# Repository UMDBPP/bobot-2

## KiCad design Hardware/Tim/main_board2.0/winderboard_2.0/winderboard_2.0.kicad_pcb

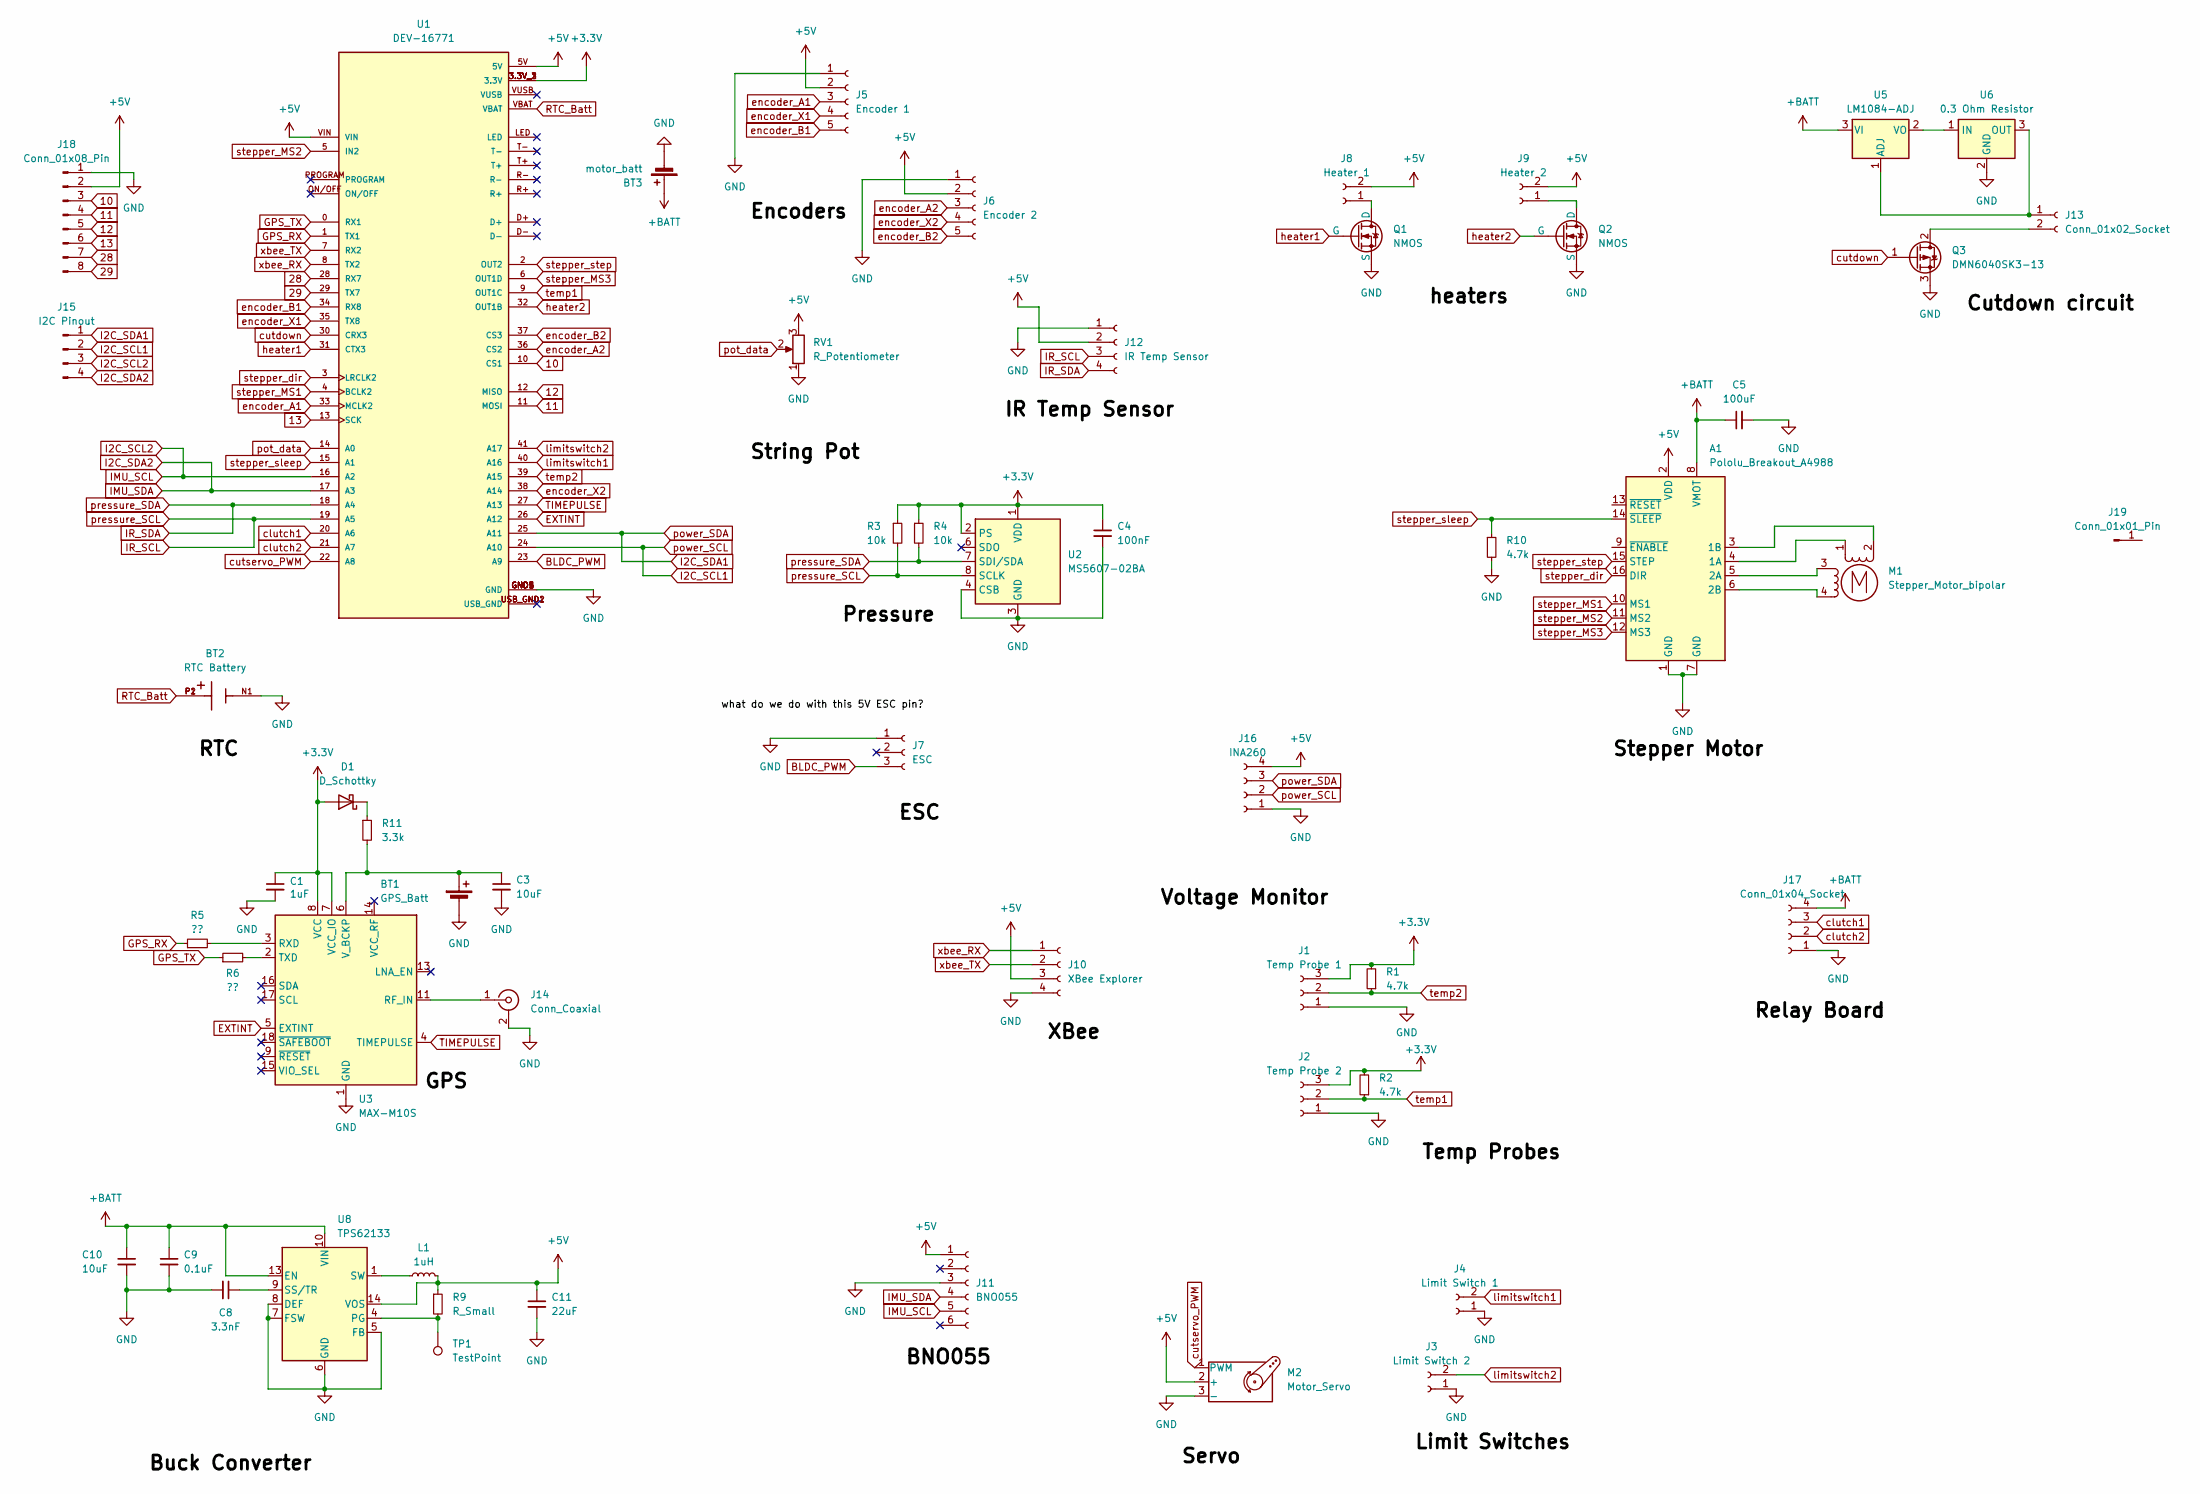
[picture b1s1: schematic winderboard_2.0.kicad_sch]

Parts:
A1: Pololu_Breakout_A4988; Pololu_Breakout-16_15.2x20.3mm
BT1: GPS_Batt; SEIKO_ML414H_IV01E
BT2: RTC Battery; BAT_BAT-HLD-001; PARTREV C
BT3: motor_batt; AMASS_XT30PW-M_1x02_P2.50mm_Horizontal
C1: 1uF; C_0603_1608Metric_Pad1.08x0.95mm_HandSolder
C3, C10: 10uF; C_0603_1608Metric_Pad1.08x0.95mm_HandSolder
C4: 100nF; C_0603_1608Metric_Pad1.08x0.95mm_HandSolder
C5: 100uF; C_0603_1608Metric_Pad1.08x0.95mm_HandSolder
C8: 3.3nF; C_0603_1608Metric_Pad1.08x0.95mm_HandSolder
C9: 0.1uF; C_0603_1608Metric_Pad1.08x0.95mm_HandSolder
C11: 22uF; C_0603_1608Metric_Pad1.08x0.95mm_HandSolder
D1: D_Schottky; D_SOD-123F
J1: Temp Probe 1; JST_XH_B3B-XH-A_1x03_P2.50mm_Vertical
J2: Temp Probe 2; JST_XH_B3B-XH-A_1x03_P2.50mm_Vertical
J3: Limit Switch 2; JST_XH_B2B-XH-A_1x02_P2.50mm_Vertical
J4: Limit Switch 1; JST_XH_B2B-XH-A_1x02_P2.50mm_Vertical
J5: Encoder 1; JST_XH_B5B-XH-A_1x05_P2.50mm_Vertical
J6: Encoder 2; JST_XH_B5B-XH-A_1x05_P2.50mm_Vertical
J7: ESC; JST_XH_B3B-XH-A_1x03_P2.50mm_Vertical
J8: Heater 1; JST_XH_B2B-XH-A_1x02_P2.50mm_Vertical
J9: Heater 2; JST_XH_B2B-XH-A_1x02_P2.50mm_Vertical
J10: XBee Explorer
J11: BNO055
J12: IR Temp Sensor; JST_XH_B4B-XH-A_1x04_P2.50mm_Vertical
J13: Conn_01x02_Socket; PinHeader_1x02_P2.54mm_Vertical
J14: Conn_Coaxial; U.FL_Molex_MCRF_73412-0110_Vertical
J15: I2C Pinout; PinHeader_1x04_P2.54mm_Vertical
J16: INA260; JST_XH_B4B-XH-A_1x04_P2.50mm_Vertical
J17: Conn_01x04_Socket; JST_XH_B4B-XH-A_1x04_P2.50mm_Vertical
J18: Conn_01x08_Pin; PinHeader_1x08_P2.54mm_Vertical
J19: Conn_01x01_Pin; MountingHole_3.2mm_M3_DIN965_Pad
L1: 1uH; L_Coilcraft_XxL4040
M1: Stepper_Motor_bipolar; JST_XH_B4B-XH-A_1x04_P2.50mm_Vertical
M2: Motor_Servo; JST_XH_B3B-XH-A_1x03_P2.50mm_Vertical
Q1, Q2: NMOS; SOT-23-3
Q3: DMN6040SK3-13; TO-252-2
R1, R2, R10: 4.7k; R_0603_1608Metric_Pad0.98x0.95mm_HandSolder
R3, R4: 10k; R_0603_1608Metric_Pad0.98x0.95mm_HandSolder
R5, R6: ??; R_0603_1608Metric_Pad0.98x0.95mm_HandSolder
R9: R_Small; R_0603_1608Metric_Pad0.98x0.95mm_HandSolder
R11: 3.3k; R_0603_1608Metric_Pad0.98x0.95mm_HandSolder
RV1: R_Potentiometer; JST_XH_B3B-XH-A_1x03_P2.50mm_Vertical
TP1: TestPoint; TestPoint_Loop_D2.54mm_Drill1.5mm_Beaded
U1: DEV-16771; MODULE_DEV-16771; PARTREV 4.1
U2: MS5607-02BA; LGA-8_3x5mm_P1.25mm
U3: MAX-M10S; ublox_MAX
U5: LM1084-ADJ; TO-263-3_TabPin2
U6: 0.3 Ohm Resistor; TO-263-2
U8: TPS62133; VQFN-16-1EP_3x3mm_P0.5mm_EP1.68x1.68mm_ThermalVias

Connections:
10: J18.3, U1.10 (CS1)
11: J18.4, U1.11 (MOSI)
12: J18.5, U1.12 (MISO)
13: J18.6, U1.13 (SCK)
28: J18.7, U1.28 (RX7)
29: J18.8, U1.29 (TX7)
+3.3V: C1.1, C4.1, D1.2 (A), J1.3, J2.3, R1.2, R2.2, R3.1, R4.1, U1.3.3V_1 (3.3V), U1.3.3V_2 (3.3V), U1.3.3V_3 (3.3V), U2.1 (VDD), U2.2 (PS), U3.7 (VCC_IO), U3.8 (VCC)
+5V: A1.2 (VDD), C11.1, J5.2, J6.2, J8.2, J9.2, J10.3, J11.1, J12.2, J16.4, J18.2, L1.2, M2.2 (+), R9.1, RV1.3, U1.5V, U1.VIN, U8.14 (VOS)
+BATT: A1.8 (VMOT), BT3.1 (+), C5.1, C9.1, C10.1, J17.4, U5.3 (VI), U8.10 (VIN), U8.11 (VIN), U8.12 (VIN), U8.13 (EN)
BLDC_PWM: J7.3, U1.23 (A9)
EXTINT: U1.26 (A12), U3.5 (EXTINT)
GND: A1.1 (GND), A1.7 (GND), BT1.2 (-), BT2.N1, BT3.2 (-), C1.2, C3.2, C4.2, C5.2, C8.2, C9.2, C10.2, C11.2, J1.1, J2.1, J3.1, J4.1, J5.1, J6.1, J7.1, J10.4, J11.3, J12.1, J14.2 (Ext), J16.1, J17.1, J18.1, M2.3 (-), Q1.3 (S), Q2.3 (S), Q3.3 (S), R10.2, RV1.1, U1.GND1 (GND), U1.GND2 (GND), U1.GND3 (GND), U1.GND4 (GND), U1.GND5 (GND), U2.3 (GND), U2.4 (CSB), U2.5 (CSB), U3.1 (GND), U3.10 (GND), U3.12 (GND), U6.2 (GND), U8.5 (FB), U8.6 (GND), U8.7 (FSW), U8.8 (DEF), U8.15 (GND), U8.16 (GND), U8.17 (GND)
GPS_RX: R5.1, U1.1 (TX1)
GPS_TX: R6.1, U1.0 (RX1)
I2C_SCL1: J15.2, J16.2, U1.24 (A10)
I2C_SCL2: J11.5, J15.3, U1.16 (A2)
I2C_SDA1: J15.1, J16.3, U1.25 (A11)
I2C_SDA2: J11.4, J15.4, U1.17 (A3)
IR_SCL: J12.3, R3.2, U1.19 (A5), U2.8 (SCLK)
IR_SDA: J12.4, R4.2, U1.18 (A4), U2.7 (SDI/SDA)
unnamed: A1.4 (1A), M1.1
unnamed: A1.3 (1B), M1.2 (-)
unnamed: A1.5 (2A), M1.3
unnamed: A1.6 (2B), M1.4
unnamed: BT1.1 (+), C3.1, R11.2, U3.6 (V_BCKP)
unnamed: D1.1 (K), R11.1
unnamed: J8.1, Q1.1 (D)
unnamed: J9.1, Q2.1 (D)
unnamed: J13.1, U5.1 (ADJ), U6.3 (OUT)
unnamed: J13.2, Q3.2 (D)
unnamed: J14.1 (In), U3.11 (RF_IN)
unnamed: L1.1, U8.1 (SW), U8.2 (SW), U8.3 (SW)
unnamed: R5.2, U3.3 (RXD)
unnamed: R6.2, U3.2 (TXD)
unnamed: U5.2 (VO), U6.1 (IN)
unnamed: R9.2, TP1.1, U8.4 (PG)
unnamed: C8.1, U8.9 (SS/TR)
RTC_Batt: BT2.P1, BT2.P2, U1.VBAT
TIMEPULSE: U1.27 (A13), U3.4 (TIMEPULSE)
clutch1: J17.3, U1.20 (A6)
clutch2: J17.2, U1.21 (A7)
cutdown: Q3.1 (G), U1.30 (CRX3)
cutservo_PWM: M2.1 (PWM), U1.22 (A8)
encoder_A1: J5.3, U1.33 (MCLK2)
encoder_A2: J6.3, U1.36 (CS2)
encoder_B1: J5.5, U1.34 (RX8)
encoder_B2: J6.5, U1.37 (CS3)
encoder_X1: J5.4, U1.35 (TX8)
encoder_X2: J6.4, U1.38 (A14)
heater1: Q1.2 (G), U1.31 (CTX3)
heater2: Q2.2 (G), U1.32 (OUT1B)
limitswitch1: J4.2, U1.40 (A16)
limitswitch2: J3.2, U1.41 (A17)
pot_data: RV1.2, U1.14 (A0)
stepper_MS1: A1.10 (MS1), U1.4 (BCLK2)
stepper_MS2: A1.11 (MS2), U1.5 (IN2)
stepper_MS3: A1.12 (MS3), U1.6 (OUT1D)
stepper_dir: A1.16 (DIR), U1.3 (LRCLK2)
stepper_sleep: A1.14 (~SLEEP), R10.1, U1.15 (A1)
stepper_step: A1.15 (STEP), U1.2 (OUT2)
temp1: J2.2, R2.1, U1.9 (OUT1C)
temp2: J1.2, R1.1, U1.39 (A15)
xbee_RX: J10.1, U1.8 (TX2)
xbee_TX: J10.2, U1.7 (RX2)

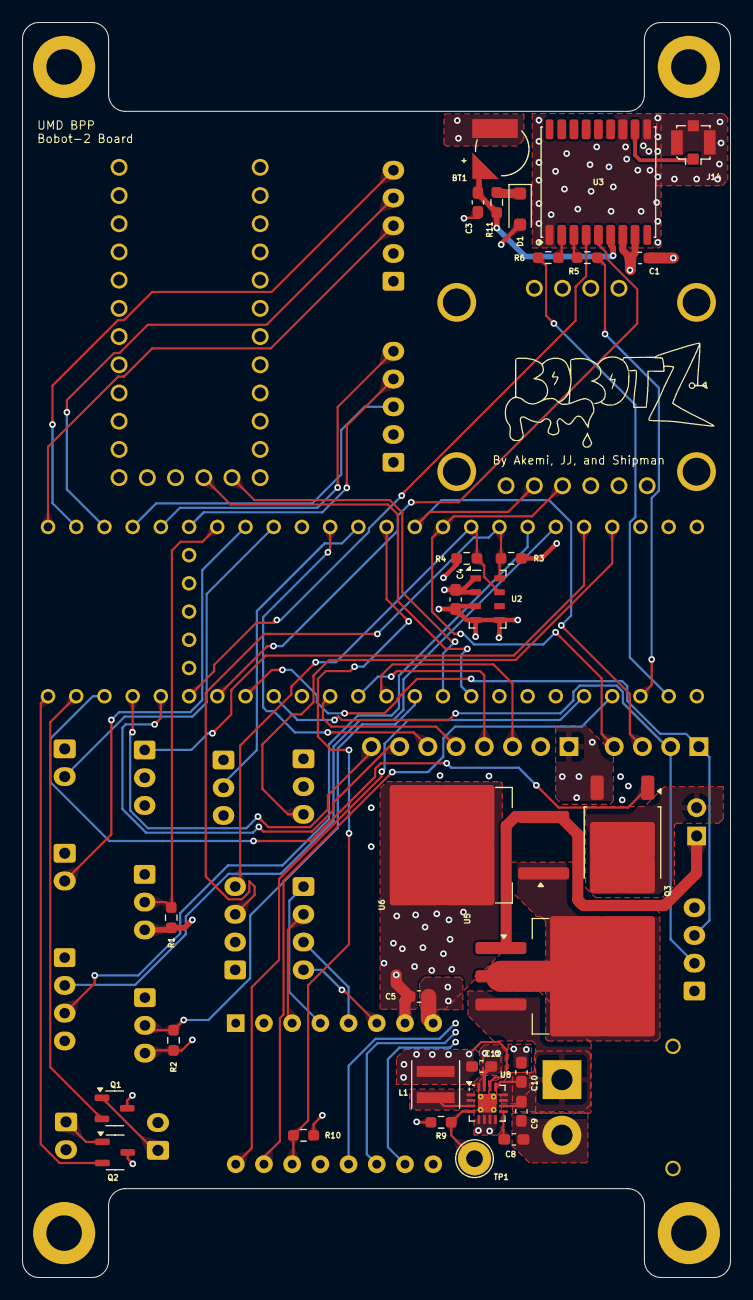
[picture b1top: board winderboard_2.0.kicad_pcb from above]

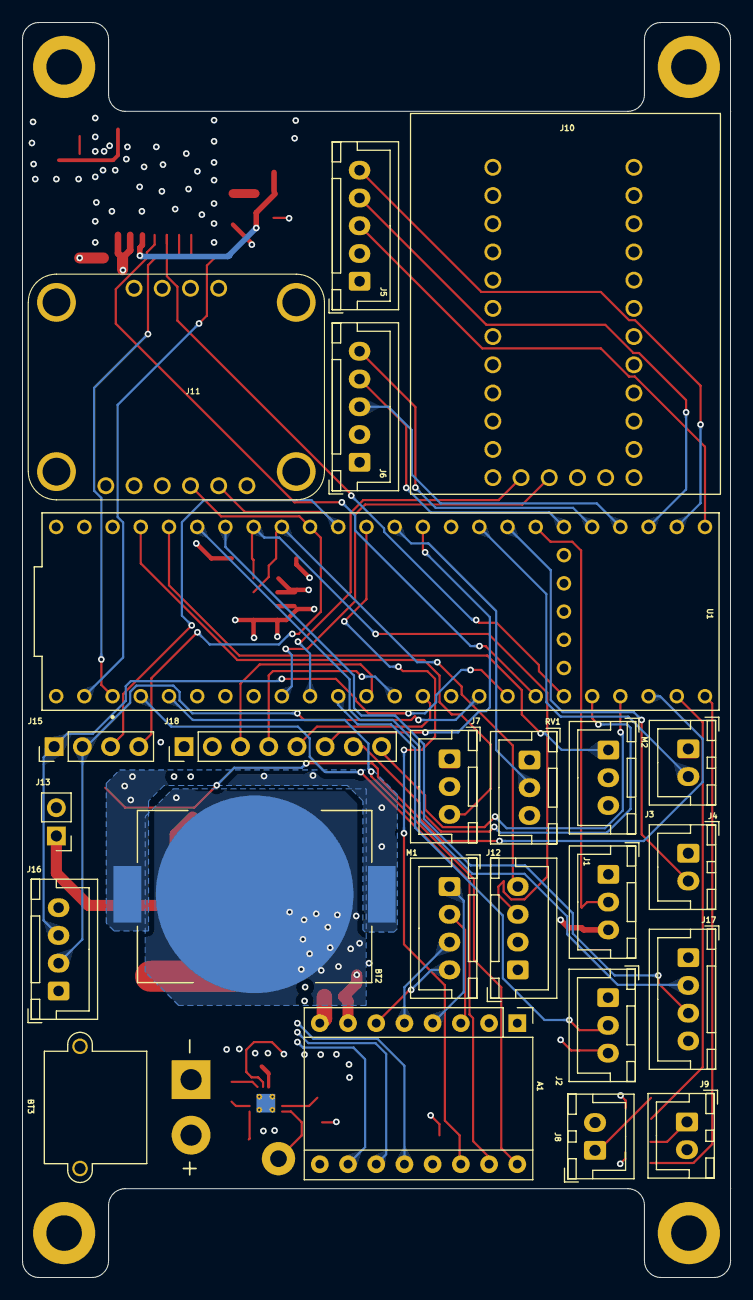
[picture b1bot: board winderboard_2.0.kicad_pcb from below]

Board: 4 copper layers, 63.8 x 113.0 mm, 58 parts (24 on the bottom side), 64 nets.

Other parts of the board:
J19#2, J19#3, J19#4: Conn_01x01_Pin; MountingHole_3.2mm_M3_DIN965_Pad

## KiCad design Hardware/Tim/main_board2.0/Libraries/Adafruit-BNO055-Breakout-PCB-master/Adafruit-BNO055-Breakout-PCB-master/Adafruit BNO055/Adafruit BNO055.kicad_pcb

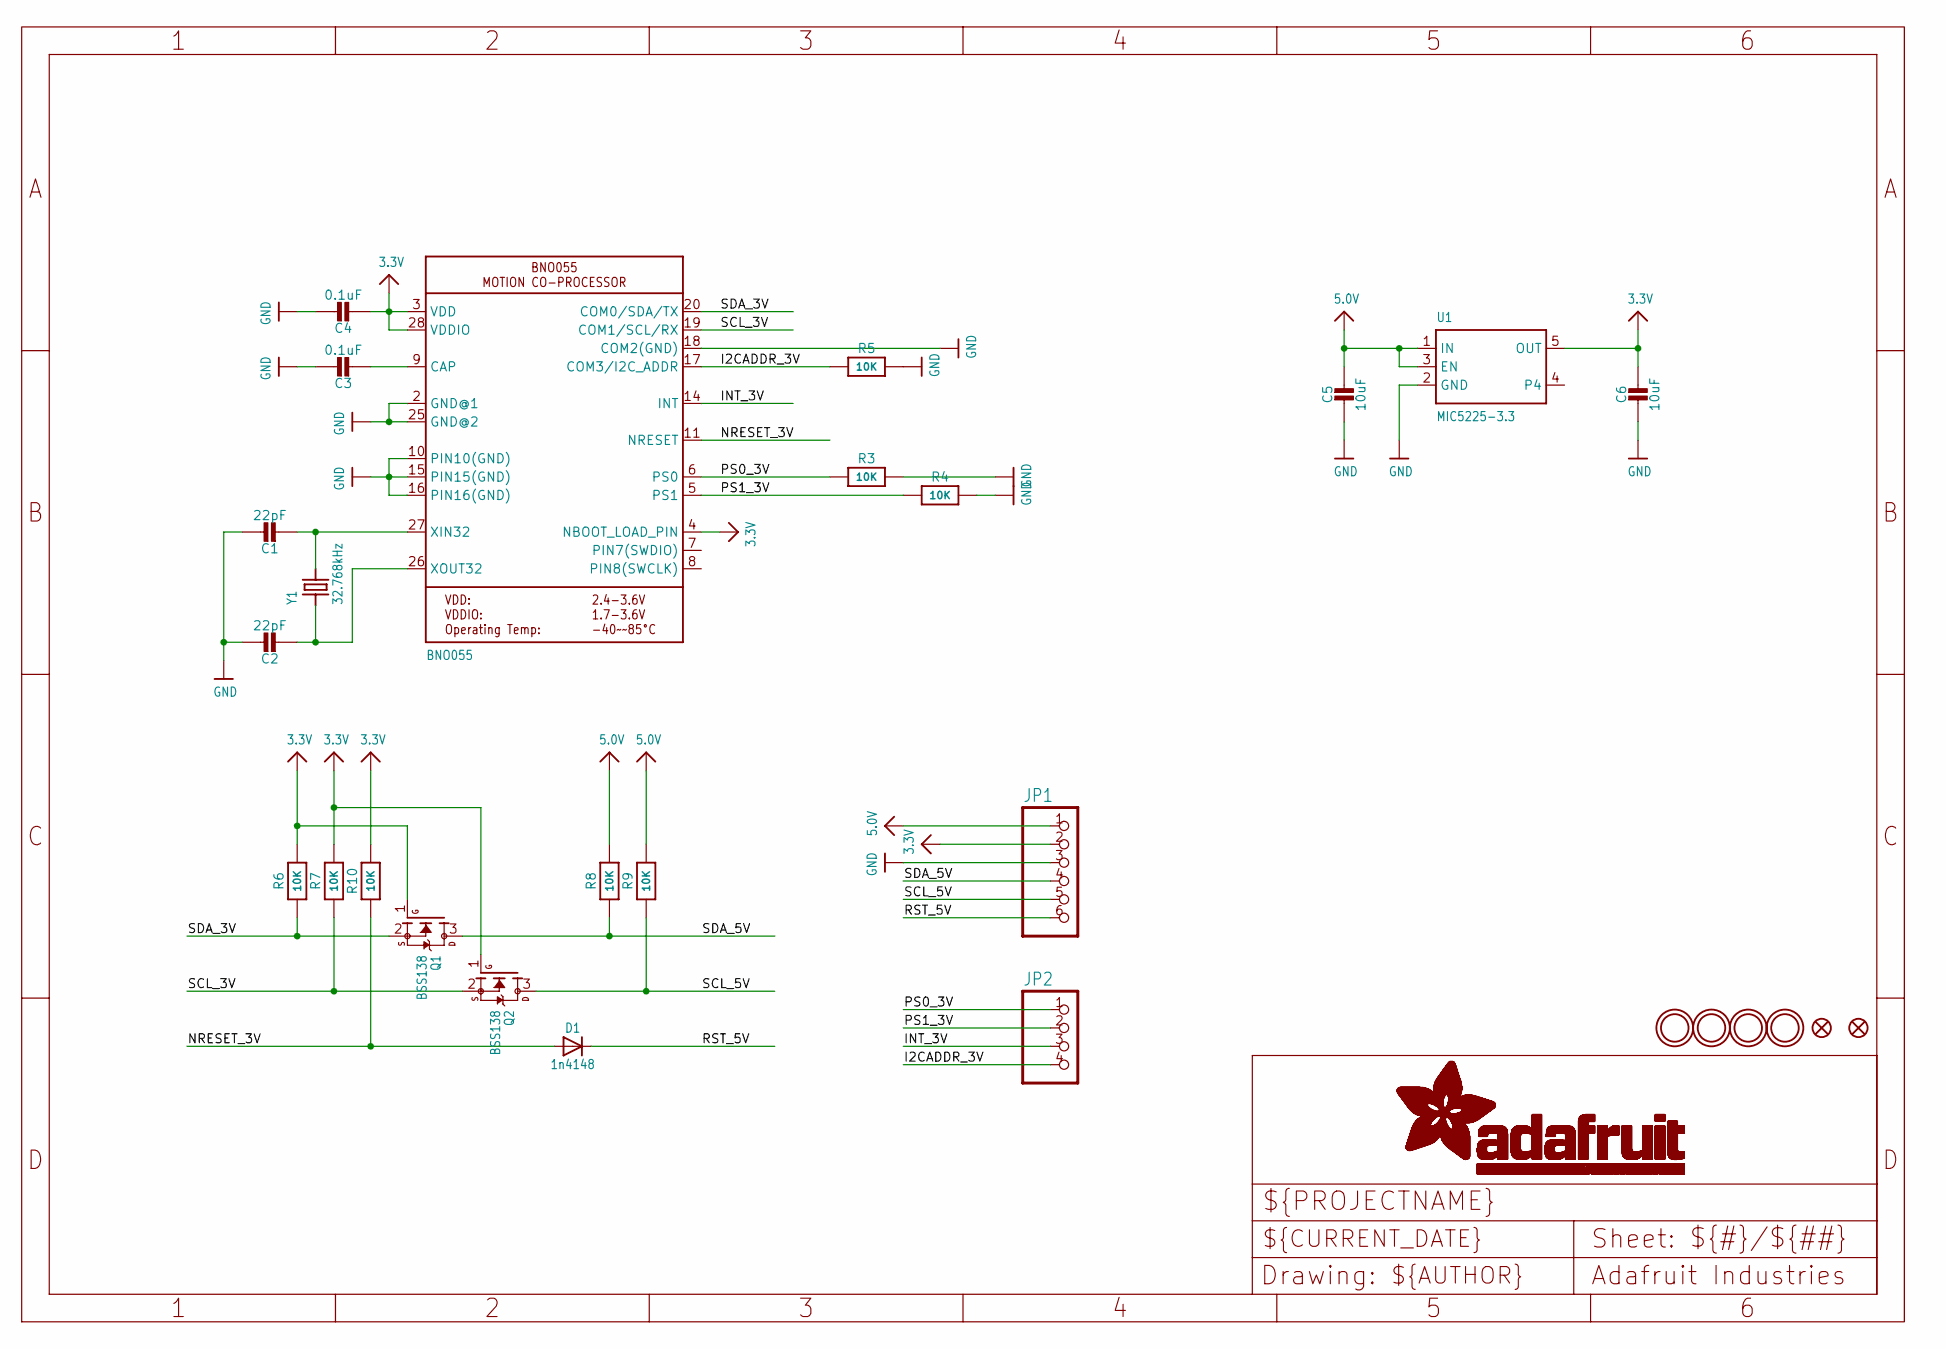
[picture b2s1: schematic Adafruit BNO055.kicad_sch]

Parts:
C1, C2: 22pF; 0805-NO
C3: 0.1uF; 0805-NO
C4: 0.1uF; 0805_10MGAP
C5: 10uF; 0805-NO
C6: 10uF; 0805_10MGAP
D1: 1n4148; SOD-323
FID1, FID2: FIDUCIAL""; FIDUCIAL_1MM
JP1: HEADER-1X676MIL; 1X06_ROUND_76
JP2: HEADER-1X476MIL; 1X04_ROUND_76
Q1, Q2: BSS138; SOT23-WIDE
R3, R4, R5, R6, R7, R10: 10K; 0805-NO
R8, R9: 10K; _0805MP
U1: MIC5225-3.3; SOT23-5
U$2: BNO055
U$29, U$30, U$31, U$32: MOUNTINGHOLE2.5_THICK; MOUNTINGHOLE_2.5_PLATED_THICK
Y1: 32.768kHz; CRYSTAL_8X3.8

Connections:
3.3V: C4.2, C6.1, JP1.2, Q1.1 (G), Q2.1 (G), R6.2, R7.2, R10.2, U1.5 (OUT), U$2.3 (VDD), U$2.4 (NBOOT_LOAD_PIN), U$2.28 (VDDIO)
5.0V: C5.1, JP1.1, R8.2, R9.2, U1.1 (IN), U1.3 (EN)
GND: C1.1, C2.1, C3.1, C4.1, C5.2, C6.2, JP1.3, R3.2, R4.2, R5.2, U1.2 (GND), U$2.2 (GND@1), U$2.10 (PIN10(GND)), U$2.15 (PIN15(GND)), U$2.16 (PIN16(GND)), U$2.18 (COM2(GND)), U$2.25 (GND@2)
I2CADDR_3V: JP2.4, R5.1, U$2.17 (COM3/I2C_ADDR)
INT_3V: JP2.3, U$2.14 (INT)
unnamed: C1.2, U$2.27 (XIN32), Y1.P$4 (2)
unnamed: C2.2, U$2.26 (XOUT32), Y1.P$1 (1)
unnamed: C3.2, U$2.9 (CAP)
NRESET_3V: D1.A, R10.1, U$2.11 (NRESET)
PS0_3V: JP2.1, R3.1, U$2.6 (PS0)
PS1_3V: JP2.2, R4.1, U$2.5 (PS1)
RST_5V: D1.C, JP1.6
SCL_3V: Q2.2 (S), R7.1, U$2.19 (COM1/SCL/RX)
SCL_5V: JP1.5, Q2.3 (D), R9.1
SDA_3V: Q1.2 (S), R6.1, U$2.20 (COM0/SDA/TX)
SDA_5V: JP1.4, Q1.3 (D), R8.1

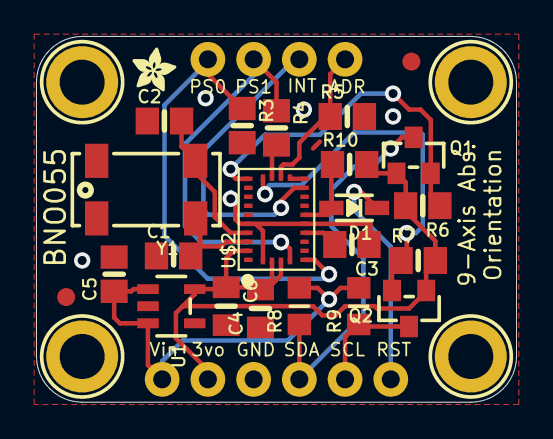
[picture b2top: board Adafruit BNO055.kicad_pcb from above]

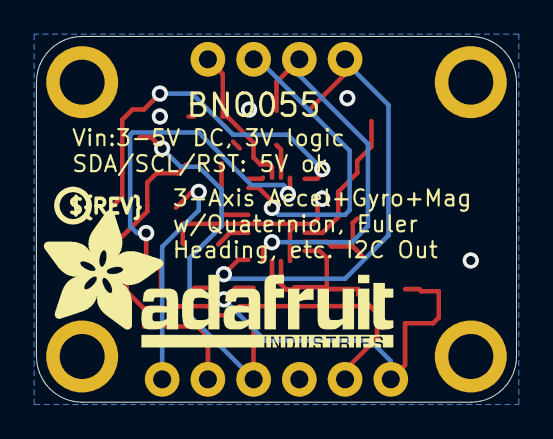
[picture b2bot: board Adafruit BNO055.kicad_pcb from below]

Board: 2 copper layers, 26.7 x 20.3 mm, 31 parts (2 on the bottom side), 16 nets.

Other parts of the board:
U$3: PCBFEAT-REV-040
U$28: ADAFRUIT_TEXT_20MM
U$33: ADAFRUIT_2.5MM

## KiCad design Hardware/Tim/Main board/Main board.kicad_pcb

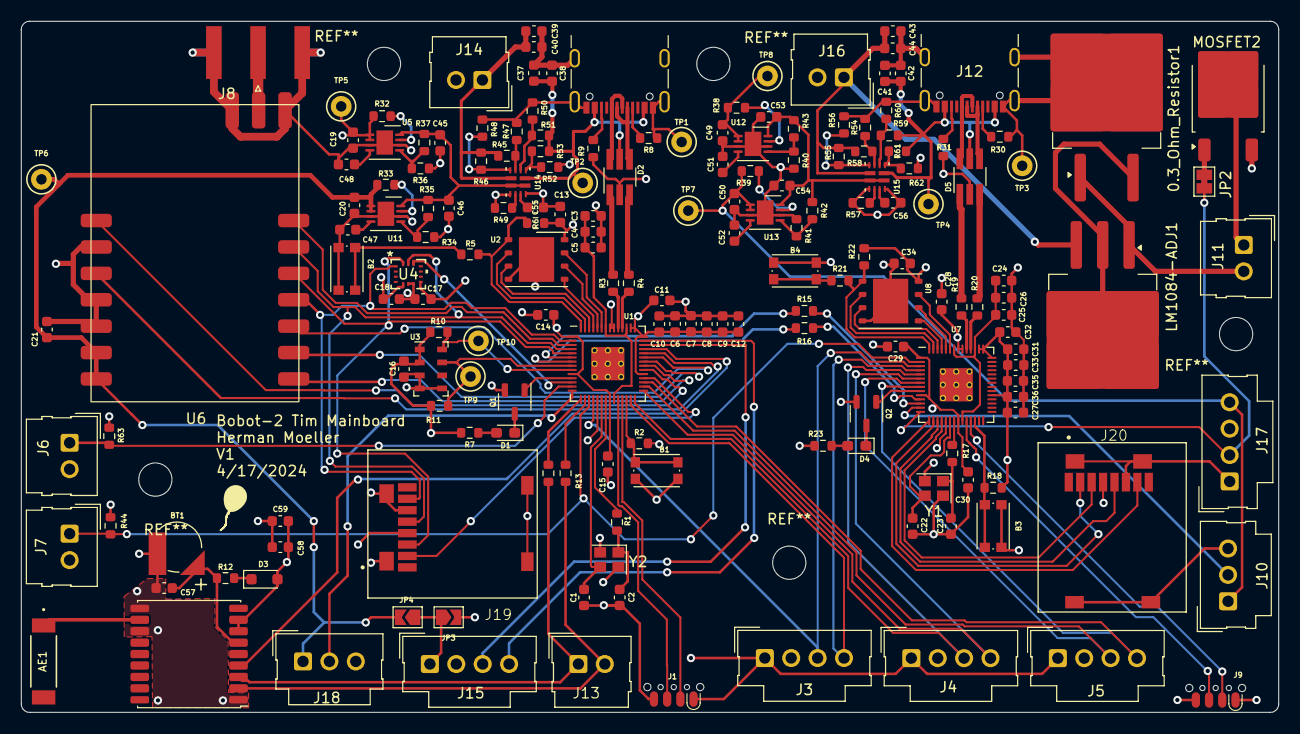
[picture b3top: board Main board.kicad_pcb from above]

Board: 4 copper layers, 121.0 x 66.5 mm, 181 parts (0 on the bottom side), 133 nets.

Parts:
0.3_Ohm_Resistor1: 03; TO-263-2
AE1: Antenna; ANT_1575AT_JOT-M
B1, B2, B3, B4: KMR2; SW_Push_1P1T_NO_CK_KMR2
BT1: ML414H IV01E; SEIKO_ML414H_IV01E
C1, C2, C22, C23: 10pF; C_0603_1608Metric
C3, C4, C7, C8, C9, C10, C12, C13, C14, C15, C16, C17, C18, C24, C25, C28, C29, C30, C31, C33, C34, C35, C36, C38, C40, C42, C44, C58: 100nF; C_0603_1608Metric
C5, C6, C19, C20, C26, C27, C37, C39, C41, C43, C45, C46, C49, C50, C53, C54, C55, C56, C59: 1uF; C_0603_1608Metric
C11, C21, C32, C57: 10uF; C_0603_1608Metric
C47, C48, C51, C52: 1nF; C_0603_1608Metric
D1, D4: LED; D_0603_1608Metric_Pad1.05x0.95mm_HandSolder
D2, D5: USBLC6-2SC6; TSOT-23-6_HandSoldering
D3: NSR0530HT1G; D_SOD-323_HandSoldering
J1, J9: SOICbite; SOIC_clipProgSmall
J2, J12: USB_C_Receptacle_USB2.0; USB_C_Receptacle_GCT_USB4105-xx-A_16P_TopMnt_Horizontal
J3, J4, J5, J15: Conn_01x04_Socket; Molex_SL_171971-0004_1x04_P2.54mm_Vertical
J6, J7, J13: Conn_01x02_Socket; Molex_SL_171971-0002_1x02_P2.54mm_Vertical
J8: U.FL; SMA_Amphenol_132289_EdgeMount
J10, J18: Conn_01x03_Socket; Molex_SL_171971-0003_1x03_P2.54mm_Vertical
J11, J14, J16: Conn_01x02_Pin; Molex_SL_171971-0002_1x02_P2.54mm_Vertical
J17: Conn_01x04_Pin; Molex_SL_171971-0004_1x04_P2.54mm_Vertical
J19, J20: Micro_SD_Card; JAE_ST1W008S4ER1500
JP2: SolderJumper_2_Bridged; SolderJumper-2_P1.3mm_Bridged_Pad1.0x1.5mm
JP3, JP4: SolderJumper_2_Open; SolderJumper-2_P1.3mm_Open_TrianglePad1.0x1.5mm
LM1084-ADJ1: LM1084-ADJ; TO-263-3_TabPin2
MOSFET2: IRF540N; TO-252-2
Q1, Q2: IRLML0060TRPBF; SOT-23-3
R1, R5, R12, R17, R21: 1k; R_0603_1608Metric
R2, R6, R10, R11, R18, R22, R44, R63: 10k; R_0603_1608Metric
R3, R4, R19, R20: 27; R_0603_1608Metric
R7, R23: 590; R_0603_1608Metric
R8, R9, R30, R31: 5.1k; R_0603_1608Metric
R13, R14, R15, R16: 0; R_0603_1608Metric
R32, R33, R34, R35, R36, R37, R38, R39, R40, R41, R42, R43: 100k; R_0603_1608Metric
R45, R58: 63.4k; R_0603_1608Metric
R46, R55: 18.2k; R_0603_1608Metric
R47, R48, R50, R52, R54, R56, R60, R62: 5k; R_0603_1608Metric
R49, R57: 21.5k; R_0603_1608Metric
R51, R59: 23.7k; R_0603_1608Metric
R53, R61: 10.2k; R_0603_1608Metric
TP1, TP2, TP3, TP4, TP5, TP6, TP7, TP8, TP9, TP10: TestPoint; TestPoint_Keystone_5000-5004_Miniature
U1, U7: RP2040; RP2040-QFN-56
U2, U8: W25Q64JVZP; WSON-8-1EP_6x5mm_P1.27mm_EP3.4x4.3mm
U3: MS5607-02BA; LGA-8_3x5mm_P1.25mm
U4: BMI270; BMI270_BOS-L
U5, U12: ADP7105ACPZ-3.3-R7; LFCSP-8-1EP_3x3mm_P0.5mm_EP1.6x2.34mm
U6: DRF1262TL
U10: MAX-M10S; ublox_MAX
U11, U13: ADP7105ACPZ-5.0-R7; LFCSP-8-1EP_3x3mm_P0.5mm_EP1.6x2.34mm
U14, U15: TPS2121RUXR; TPS2121
Y1, Y2: 12MHz; Crystal_SMD_2520-4Pin_2.5x2.0mm

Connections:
+3V3: C6.1, C7.1, C8.1, C9.1, C10.1, C11.1, C12.1, C13.1, C14.1, C15.1, C16.1, C17.2, C18.1, C19.1, C58.1, C59.1, D3.2 (A), J1.1, J3.1, J4.1, J5.1, J19.4 (VDD), JP3.2 (B), R2.1, R6.1, R7.1, R10.1, R11.1, R32.1, R44.1, R63.1, TP5.1, U1.1 (IOVDD), U1.10 (IOVDD), U1.22 (IOVDD), U1.33 (IOVDD), U1.42 (IOVDD), U1.43 (ADC_AVDD), U1.44 (VREG_IN), U1.48 (USB_VDD), U1.49 (IOVDD), U2.8 (VCC), U3.1 (VDD), U3.2 (PS), U4.5 (VDDIO), U4.8 (VDD), U5.1 (VOUT), U5.2 (SENSE), U10.7 (VCC_IO), U10.8 (VCC)
+3V3_R: C27.1, C28.1, C29.1, C30.1, C31.1, C32.1, C33.1, C34.1, C35.1, C36.1, C49.1, J9.1, J17.3, J20.4 (VDD), R18.1, R22.1, R23.1, R38.1, TP8.1, U7.1 (IOVDD), U7.10 (IOVDD), U7.22 (IOVDD), U7.33 (IOVDD), U7.42 (IOVDD), U7.43 (ADC_AVDD), U7.44 (VREG_IN), U7.48 (USB_VDD), U7.49 (IOVDD), U8.8 (VCC), U12.1 (VOUT), U12.2 (SENSE)
+5V: C20.1, C21.1, J18.1, JP4.2 (B), R33.1, TP6.1, U6.6 (VDD), U6.7 (VDD), U11.1 (VOUT), U11.2 (SENSE)
+5V_R: C50.1, J10.1, J17.4, R39.1, TP7.1, U13.1 (VOUT), U13.2 (SENSE)
+BATT: C43.1, C44.1, J16.1, LM1084-ADJ1.3 (VI), R55.2, R58.2, U15.7 (IN1)
/BUSY: U1.36 (GPIO24), U6.9 (BUSY)
/CROSS_PRIMRX_REDTX: R16.2, U7.11 (GPIO8)
/CROSS_PRIMTX_REDRX: R15.2, U7.12 (GPIO9)
/CUT: J17.2, JP2.1 (A), U7.14 (GPIO11)
/Ch.1A: J3.3, U1.18 (GPIO15), U7.3 (GPIO1)
/Ch.1B: J3.4, U1.27 (GPIO16), U7.4 (GPIO2)
/Ch.2A: J4.3, U1.28 (GPIO17), U7.5 (GPIO3)
/Ch.2B: J4.4, U1.29 (GPIO18), U7.6 (GPIO4)
/Ch.3A: J5.3, U1.30 (GPIO19), U7.7 (GPIO5)
/Ch.3B: J5.4, U1.31 (GPIO20), U7.8 (GPIO6)
/D1: Q1.1 (G), U1.11 (GPIO8)
/D1_R: Q2.1 (G), U7.9 (GPIO7)
/D+: D2.6 (L1), J2.A6 (D+), J2.B6 (D+)
/D-: D2.4 (L2), J2.A7 (D-), J2.B7 (D-)
/DIO1: U1.35 (GPIO23), U6.8 (DIO1)
/DIR: J15.4, U1.41 (GPIO29_ADC3)
/GPS_RX: R14.1, U1.15 (GPIO12)
/GPS_TX: R13.1, U1.16 (GPIO13)
/LS1: J7.1, R44.2, U1.17 (GPIO14), U7.2 (GPIO0)
/LS2: J6.1, R63.2, U1.13 (GPIO10)
/PWM_EMRG_REL: J10.2, U7.13 (GPIO10)
/PWM_MC: J18.2, U1.14 (GPIO11)
/QSPI_SCLK: U1.52 (QSPI_SCLK), U2.6 (CLK)
/QSPI_SD0: U1.53 (QSPI_SD0), U2.5 (DI(IO0))
/QSPI_SD1: U1.55 (QSPI_SD1), U2.2 (DO(IO1))
/QSPI_SD2: U1.54 (QSPI_SD2), U2.3 (IO2)
/QSPI_SD3: U1.51 (QSPI_SD3), U2.7 (IO3)
/QSPI_SS: R5.2, R6.2, U1.56 (QSPI_SS), U2.1 (~CS)
/R_QSPI_SCLK: U7.52 (QSPI_SCLK), U8.6 (CLK)
/R_QSPI_SD0: U7.53 (QSPI_SD0), U8.5 (DI(IO0))
/R_QSPI_SD1: U7.55 (QSPI_SD1), U8.2 (DO(IO1))
/R_QSPI_SD2: U7.54 (QSPI_SD2), U8.3 (IO2)
/R_QSPI_SD3: U7.51 (QSPI_SD3), U8.7 (IO3)
/R_QSPI_SS: R21.2, R22.2, U7.56 (QSPI_SS), U8.1 (~CS)
/R_USB_D+: D5.1 (L1), R19.2
/R_USB_D-: D5.3 (L2), R20.2
/SCL: R10.2, TP10.1, U1.9 (GPIO7), U3.8 (SCLK)
/SDA: R11.2, TP9.1, U1.8 (GPIO6), U3.7 (SDI/SDA)
/SPI0_CS_RAD: U1.3 (GPIO1), U6.14 (NSS)
/SPI0_CS_SD: J19.2 (DAT3/CD), U1.32 (GPIO21)
/SPI0_CS_SD_R: J20.2 (DAT3/CD), U7.16 (GPIO13)
/SPI0_PICO: J19.3 (CMD), U1.5 (GPIO3), U4.14 (SDX), U6.12 (MOSI)
/SPI0_PICO_R: J20.3 (CMD), U7.18 (GPIO15)
/SPI0_POCI: J19.7 (DAT0), U1.2 (GPIO0), U4.1 (SDO), U6.11 (MISO)
/SPI0_POCI_R: J20.7 (DAT0), U7.15 (GPIO12)
/SPI0_SCK: J19.5 (CLK), U1.4 (GPIO2), U4.13 (SCX), U6.13 (SCK)
/SPI0_SCK_R: J20.5 (CLK), U7.17 (GPIO14)
/SPIO_CS_IMU: U1.12 (GPIO9), U4.12 (CSB)
/STEP: J15.3, U1.40 (GPIO28_ADC2)
/SW: U1.34 (GPIO22), U6.1 (SW)
/SWCLK: J1.3, U1.24 (SWCLK)
/SWCLK_R: J9.3, U7.24 (SWCLK)
/SWD: J1.2, U1.25 (SWD)
/SWD_R: J9.2, U7.25 (SWD)
/TIMEPULSE: U1.39 (GPIO27_ADC1), U10.4 (TIMEPULSE)
/TXEN: U1.38 (GPIO26_ADC0), U6.3 (TXEN)
/USB_D+: D2.1 (L1), R3.2
/USB_D-: D2.3 (L2), R4.2
/V_BCKP: BT1.1 (+), C57.1, R12.2, U10.6 (V_BCKP)
/~RST: U1.37 (GPIO25), U6.10 (RST)
GND: 0.3_Ohm_Resistor1.3 (Gnd), B1.1, B2.1, B3.1, B4.1, BT1.2 (-), C1.1, C2.1, C3.2, C4.2, C5.2, C6.2, C7.2, C8.2, C9.2, C10.2, C11.2, C12.2, C13.2, C14.2, C15.2, C16.2, C17.1, C18.2, C19.2, C20.2, C21.2, C22.1, C23.1, C24.2, C25.2, C26.2, C27.2, C28.2, C29.2, C30.2, C31.2, C32.2, C33.2, C34.2, C35.2, C36.2, C37.2, C38.2, C39.2, C40.2, C41.2, C42.2, C43.2, C44.2, C45.2, C46.2, C47.2, C48.2, C49.2, C50.2, C51.2, C52.2, C53.2, C54.2, C55.1, C56.1, C57.2, C58.2, C59.2, D2.2 (VN), D5.2 (VN), J1.4, J2.A1 (GND), J2.A12 (GND), J2.B1 (GND), J2.B12 (GND), J2.S1 (SHIELD), J3.2, J4.2, J5.2, J6.2, J7.2, J8.2 (Ext), J9.4, J10.3, J12.A1 (GND), J12.A12 (GND), J12.B1 (GND), J12.B12 (GND), J12.S1 (SHIELD), J14.2, J15.2, J16.2, J17.1, J18.3, J19.6 (VSS), J19.9 (SHIELD), J20.6 (VSS), J20.9 (SHIELD), MOSFET2.3 (S), Q1.2 (S), Q2.2 (S), R8.2, R9.2, R30.2, R31.2, R34.1, R36.1, R40.1, R41.1, R47.1, R48.1, R49.2, R50.1, R52.1, R54.1, R56.1, R57.2, R60.1, R62.1, TP1.1, TP3.1, U1.19 (TESTEN), U1.57 (GND), U2.4 (GND), U2.9 (EP), U3.3 (GND), U3.4 (CSB), U3.5 (CSB), U4.6 (GNDIO), U4.7 (GND), U5.3 (GND), U5.6 (GND), U5.9 (GND), U6.2 (GND), U6.4 (GND), U6.5 (GND), U6.15 (GND), U6.17 (GND), U7.19 (TESTEN), U7.57 (GND), U8.4 (GND), U8.9 (EP), U10.1 (GND), U10.10 (GND), U10.12 (GND), U11.3 (GND), U11.6 (GND), U11.9 (GND), U12.3 (GND), U12.6 (GND), U12.9 (GND), U13.3 (GND), U13.6 (GND), U13.9 (GND), U14.9 (ST), U14.12 (GND), U15.9 (ST), U15.12 (GND), Y1.2, Y1.4, Y2.2, Y2.4
unnamed: AE1.1 (A), U10.11 (RF_IN)
unnamed: B2.2, R5.1
unnamed: B4.2, R21.1
unnamed: C2.2, R1.1, Y2.1
unnamed: C23.2, R17.1, Y1.1
unnamed: D1.2 (A), R7.2
unnamed: D1.1 (K), Q1.3 (D)
unnamed: D3.1 (K), R12.1
unnamed: D4.2 (A), R23.2
unnamed: D4.1 (K), Q2.3 (D)
unnamed: D5.6 (L1), J12.A6 (D+), J12.B6 (D+)
unnamed: D5.4 (L2), J12.A7 (D-), J12.B7 (D-)
unnamed: J2.A5 (CC1), R8.1
unnamed: J2.B5 (CC2), R9.1
unnamed: J8.1 (In), U6.16 (ANT)
unnamed: J11.1, MOSFET2.2 (D)
unnamed: 0.3_Ohm_Resistor1.1, J11.2, LM1084-ADJ1.1 (ADJ)
unnamed: J12.A5 (CC1), R30.1
unnamed: J12.B5 (CC2), R31.1
unnamed: J13.1, R14.2, U10.3 (RXD)
unnamed: J13.2, R13.2, U10.2 (TXD)
unnamed: C39.1, C40.1, J14.1, R45.2, R46.2, U14.7 (IN1)
unnamed: J15.1, JP3.1 (A), JP4.1 (A)
unnamed: JP2.2 (B), MOSFET2.1 (G)
unnamed: 0.3_Ohm_Resistor1.2, LM1084-ADJ1.2 (VO)
unnamed: R15.1, U1.6 (GPIO4)
unnamed: R16.1, U1.7 (GPIO5)
unnamed: B1.2, R2.2, U1.26 (RUN)
unnamed: R4.1, U1.46 (USB_DM)
unnamed: R3.1, U1.47 (USB_DP)
unnamed: C3.1, C4.1, C5.1, U1.23 (DVDD), U1.45 (VREG_VOUT), U1.50 (DVDD)
unnamed: C1.2, U1.20 (XIN), Y2.3
unnamed: R1.2, U1.21 (XOUT)
unnamed: R36.2, R37.1, U5.5 (EN/UVLO)
unnamed: R32.2, U5.7 (PG)
unnamed: C48.1, U5.4 (SS)
unnamed: B3.2, R18.2, U7.26 (RUN)
unnamed: R20.1, U7.46 (USB_DM)
unnamed: R19.1, U7.47 (USB_DP)
unnamed: C24.1, C25.1, C26.1, U7.23 (DVDD), U7.45 (VREG_VOUT), U7.50 (DVDD)
unnamed: C22.2, U7.20 (XIN), Y1.3
unnamed: R17.2, U7.21 (XOUT)
unnamed: R34.2, R35.1, U11.5 (EN/UVLO)
unnamed: R33.2, U11.7 (PG)
unnamed: C47.1, U11.4 (SS)
unnamed: C45.1, C46.1, R35.2, R37.2, U5.8 (VIN), U11.8 (VIN), U14.1 (OUT), U14.8 (OUT)
unnamed: R40.2, R43.1, U12.5 (EN/UVLO)
unnamed: R38.2, U12.7 (PG)
unnamed: C51.1, U12.4 (SS)
unnamed: C53.1, C54.1, R42.2, R43.2, U12.8 (VIN), U13.8 (VIN), U15.1 (OUT), U15.8 (OUT)
unnamed: R41.2, R42.1, U13.5 (EN/UVLO)
unnamed: R39.2, U13.7 (PG)
unnamed: C52.1, U13.4 (SS)
unnamed: R52.2, R53.1, U14.3 (CP2)
unnamed: R49.1, U14.10 (ILM)
unnamed: R45.1, R47.2, U14.5 (OV1)
unnamed: R50.2, R51.1, U14.4 (OV2)
unnamed: R46.1, R48.2, U14.6 (PR1)
unnamed: C55.2, U14.11 (SS)
unnamed: R61.1, R62.2, U15.3 (CP2)
unnamed: R57.1, U15.10 (ILM)
unnamed: R54.2, R58.1, U15.5 (OV1)
unnamed: R59.1, R60.2, U15.4 (OV2)
unnamed: R55.1, R56.2, U15.6 (PR1)
unnamed: C56.2, U15.11 (SS)
VBUS: C37.1, C38.1, D2.5 (VP), J2.A4 (VBUS), J2.A9 (VBUS), J2.B4 (VBUS), J2.B9 (VBUS), R51.2, R53.2, TP2.1, U14.2 (IN2)
VCC: C41.1, C42.1, D5.5 (VP), J12.A4 (VBUS), J12.A9 (VBUS), J12.B4 (VBUS), J12.B9 (VBUS), R59.2, R61.2, TP4.1, U15.2 (IN2)

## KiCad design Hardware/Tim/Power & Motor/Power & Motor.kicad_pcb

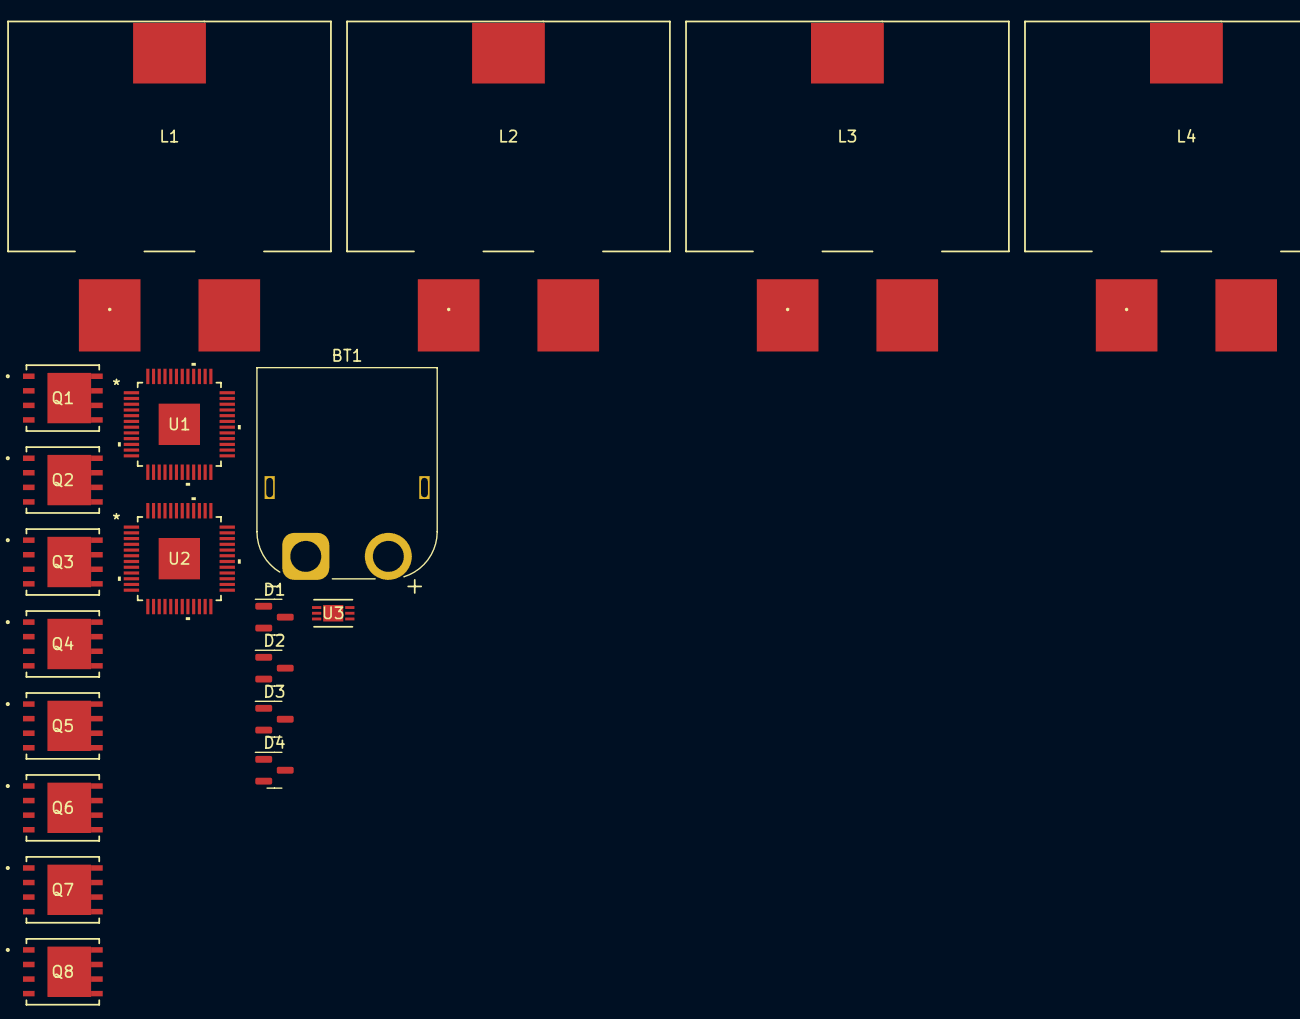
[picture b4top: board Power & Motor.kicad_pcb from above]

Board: 2 copper layers, 20 parts (0 on the bottom side), 30 nets, no tracks yet.

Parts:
BT1: Battery; AMASS_XT60PW-M_1x02_P7.20mm_Horizontal
D1, D2, D3, D4: CMPD3003A; SOT-23
L1, L2, L3, L4: 10uH; L_PQ2614B
Q1, Q2, Q5, Q6: BSC520N15NS3; Infineon 8-PowerTDFN
Q3, Q4, Q7, Q8: BSC093N15NS5; Infineon 8-PowerTDFN
U1, U2: LTC7810
U3: LTC6908-2; LTC6908-DFN

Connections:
+24V: L1.2, L2.2, L3.2, L4.2, U1.1 (SENSE1-), U1.11 (EXTVCC), U1.12 (SENSE2-), U2.1 (SENSE1-), U2.11 (EXTVCC), U2.12 (SENSE2-)
+BATT: BT1.1 (+), Q1.3 (D), Q3.3 (D), Q5.3 (D), Q7.3 (D), U1.35 (VIN), U2.35 (VIN)
/CLK1: U1.4 (PLLIN/SPREAD), U3.4 (OUT1), U3.6 (MOD)
/CLK2: U2.4 (PLLIN/SPREAD), U3.5 (OUT2)
/DRVCC1: D1.2 (A), D2.2 (A), U1.10 (NDRV), U1.26 (DRVCC), U2.10 (NDRV), U2.26 (DRVCC)
/DRVCC2: D3.2 (A), D4.2 (A)
/INTVCC1: U1.3 (INTVCC), U1.8 (MODE), U1.14 (VFB2), U3.2 (V+)
/INTVCC2: U2.3 (INTVCC), U2.8 (MODE), U2.14 (VFB2)
/ITH: U1.46 (ITH1), U2.46 (ITH1)
/LVC: U1.29 (RUN2), U1.32 (RUN1), U2.29 (RUN2), U2.32 (RUN1)
/SS: U1.45 (TRACK/SS1), U2.45 (TRACK/SS1)
GND: BT1.2 (-), Q2.1 (S), Q4.1 (S), Q6.1 (S), Q8.1 (S), U1.5 (SGND), U1.25 (PGND), U1.EPAD, U2.5 (SGND), U2.25 (PGND), U2.EPAD, U3.3 (GND), U3.7 (GND)
unnamed: D1.1 (K), U1.40 (BOOST1)
unnamed: D2.1 (K), U1.21 (BOOST2)
unnamed: D3.1 (K), U2.40 (BOOST1)
unnamed: D4.1 (K), U2.21 (BOOST2)
unnamed: Q1.2 (G), U1.42 (TG1)
unnamed: L1.1, Q1.1 (S), Q2.3 (D), U1.41 (SW1)
unnamed: Q2.2 (G), U1.37 (BG1)
unnamed: Q3.2 (G), U1.19 (TG2)
unnamed: L2.1, Q3.1 (S), Q4.3 (D), U1.20 (SW2)
unnamed: Q4.2 (G), U1.24 (BG2)
unnamed: Q5.2 (G), U2.42 (TG1)
unnamed: L3.1, Q5.1 (S), Q6.3 (D), U2.41 (SW1)
unnamed: Q6.2 (G), U2.37 (BG1)
unnamed: Q7.2 (G), U2.19 (TG2)
unnamed: L4.1, Q7.1 (S), Q8.3 (D), U2.20 (SW2)
unnamed: Q8.2 (G), U2.24 (BG2)
unnamed: U1.7 (REGSD), U1.9 (OVLO), U1.15 (ITH2), U1.16 (TRACK/SS2)
unnamed: U2.7 (REGSD), U2.9 (OVLO), U2.15 (ITH2), U2.16 (TRACK/SS2)
